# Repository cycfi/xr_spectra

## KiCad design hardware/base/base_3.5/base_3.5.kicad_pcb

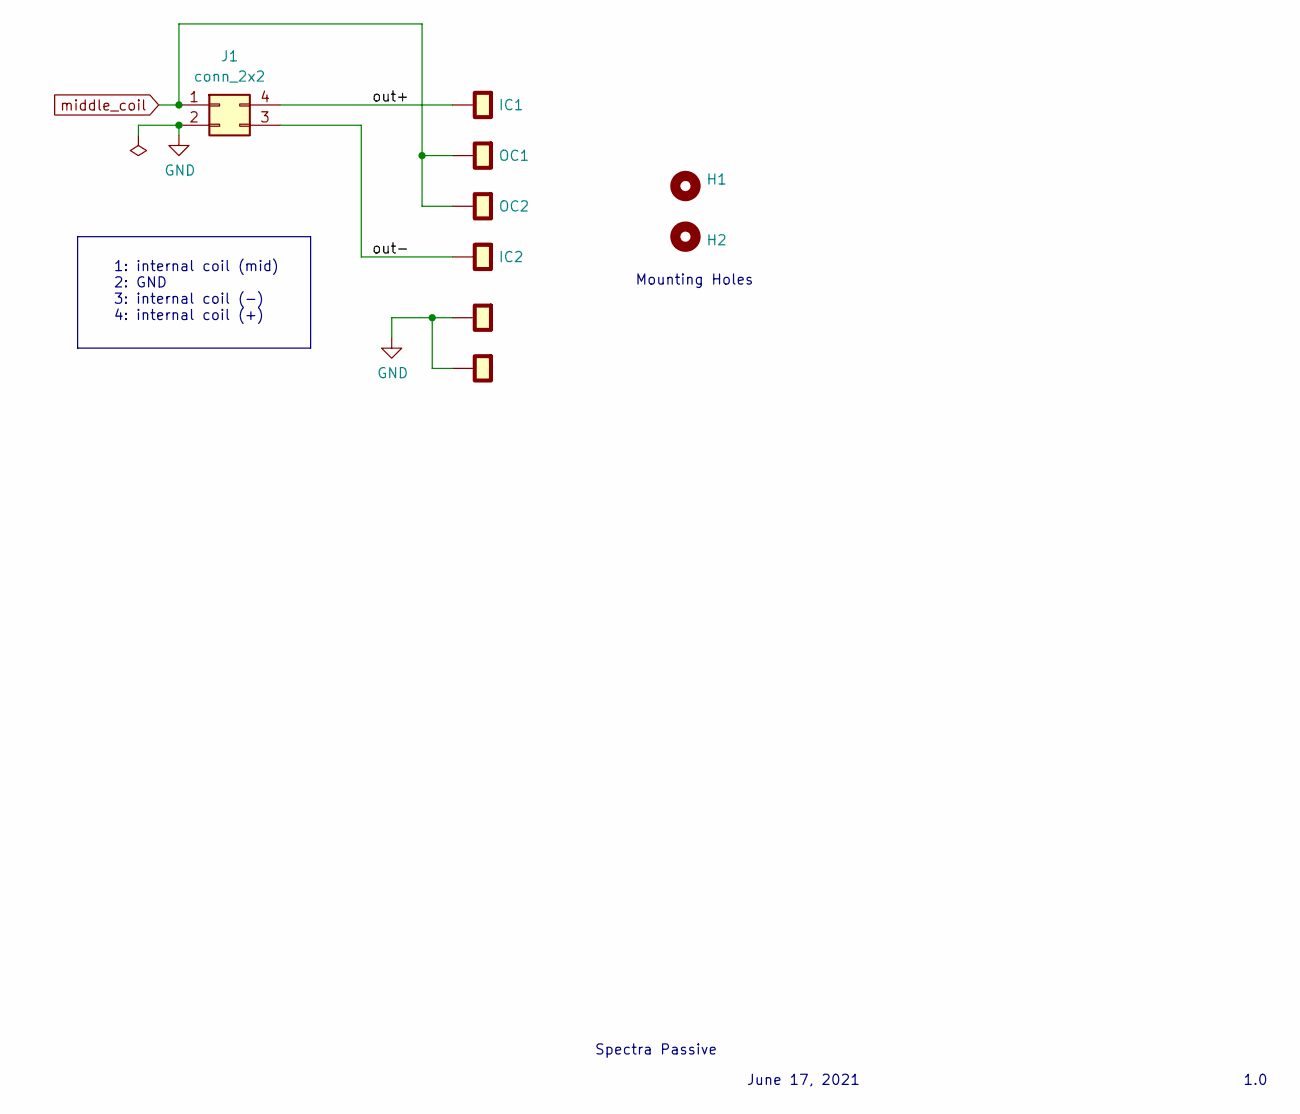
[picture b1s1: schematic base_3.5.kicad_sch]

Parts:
H1, H2: MountingHole
H5, H6: single_pad; rail_slot_3.5
IC1, IC2: single_pad; single-pad-1.6x1.6_circular
J1: conn_2x2; pin_header_2x2p_2.00mm_smd_vertical
OC1, OC2: single_pad; single-pad-1.6x1.6_circular

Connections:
/out+: IC1.1, J1.4
/out-: IC2.1, J1.3
GND: H5.1, H6.1, J1.2
middle_coil: J1.1, OC1.1, OC2.1

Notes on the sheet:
Spectra Passive
1: internal coil (mid) 2: GND 3: internal coil (-) 4: internal coil (+)
1.0
Mounting Holes
June 17, 2021

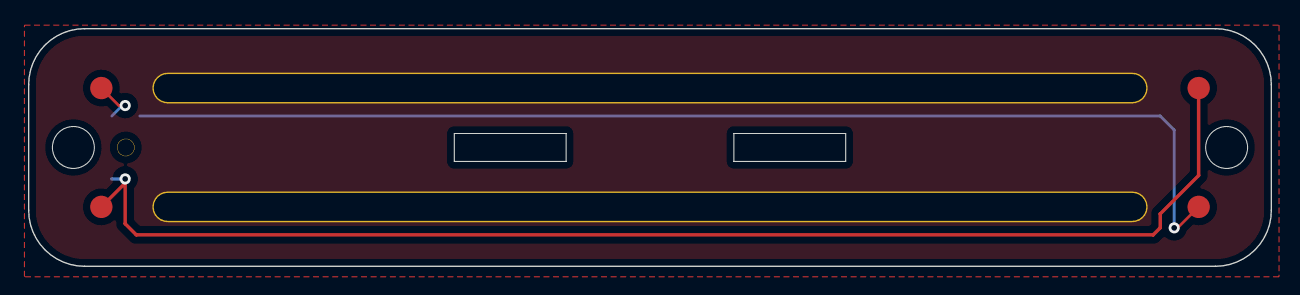
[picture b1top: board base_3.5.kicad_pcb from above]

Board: 2 copper layers, 88.9 x 17.0 mm, 9 parts (1 on the bottom side), 4 nets.

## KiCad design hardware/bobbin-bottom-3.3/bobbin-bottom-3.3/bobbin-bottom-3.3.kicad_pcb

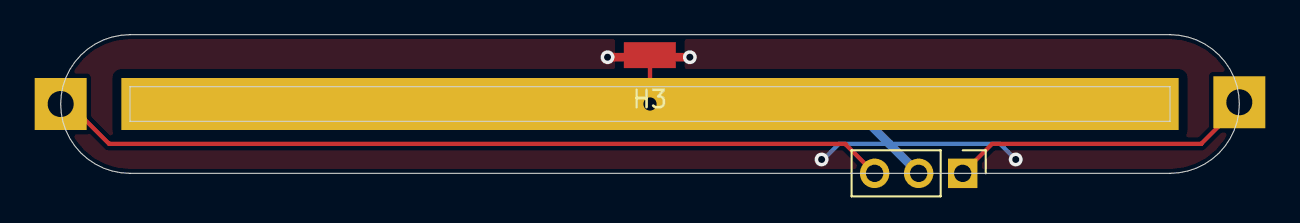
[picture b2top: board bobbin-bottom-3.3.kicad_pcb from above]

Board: 2 copper layers, 68.0 x 8.0 mm, 5 parts (0 on the bottom side), 3 nets.

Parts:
H3: single_pad_smd; single-pad-3x1.5
H4: Core GND; core-pad
IC: MountingHole_Pad; single-pad-3x3-th
OC: MountingHole_Pad; single-pad-3x3-th
Out: Conn_01x03; pad_1x03_P2.54mm

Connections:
/IC: IC.1, Out.1
/OC: OC.1, Out.3
GND: H3.1, H4.1, Out.2

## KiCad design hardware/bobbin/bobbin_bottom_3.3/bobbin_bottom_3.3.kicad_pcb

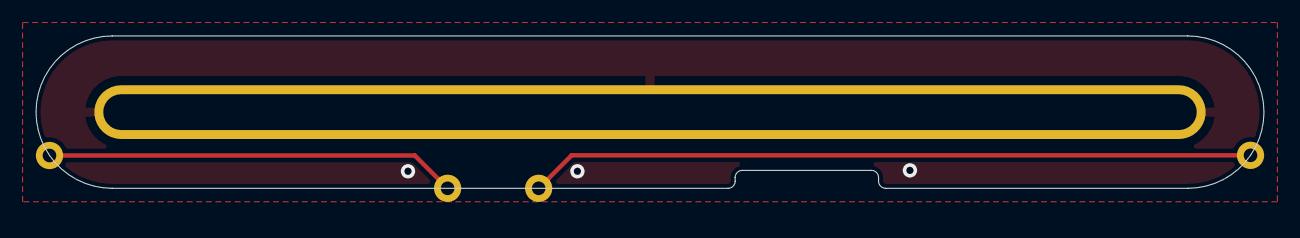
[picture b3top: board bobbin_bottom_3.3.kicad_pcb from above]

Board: 2 copper layers, 68.5 x 8.5 mm, 5 parts (0 on the bottom side), 2 nets.

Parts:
H1: single_pad; rail_slot_3.3
J1, J2: OC; single-pad-1.52x1.52-th
J3, J4: IC; single-pad-1.52x1.52-th

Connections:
/IC: J3.1, J4.1
/OC: J1.1, J2.1
